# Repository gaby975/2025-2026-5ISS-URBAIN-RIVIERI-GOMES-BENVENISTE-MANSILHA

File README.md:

# 2025-2026-5ISS-URBAIN-RIVIERI-GOMES-BENVENISTE-MANSILHA
## Introduction
The objective of this project is to develop an electronic card on which we have integrated a gas sensor manufactured in the clean room at AIME (Inter-University Micro-Nano Electronics Laboratory). The electronic board includes an analog circuit for conditioning the sensor signal, a microcontroller (ESP32) for receiving the conditioned sensor signal and communicating with the other components on the board, a LoRa module for sending sensor data over a LoRa network using Chirpstack, and a buzzer to alert when a gas concentration threshold has been exceeded.

## Gas sensor fabrication
The first step in this project is to manufacture a gas sensor. This sensor was manufactured in a clean room at the AIME (Interuniversity Micro-Nano Electronics Workshop) located on the INSA Toulouse campus. It is a semiconductor-type metal oxide gas sensor based on WO₃ nanoparticles and capable of detecting reducing gases such as ammonia (NH₃) and ethanol vapors.

The sensor is composed of several elements that are worth detailing. First, there are interdigitated aluminum combs on which WO₃ nanoparticles have been deposited and organized by dielectrophoresis. Next, there is an n-doped polysilicon heating resistor, which raises the temperature inside the sensor, improving the surface reaction between the WO₃ nanoparticles and the gas. Finally, there is an aluminum thermistor that measures the temperature inside the sensor.

The manufacturing process for this sensor involves a large number of steps, but the most important ones are the photolithography steps. Photolithography enables the formation of the different layers required for the sensor to function. We start with a Si/SiO₂ substrate onto which a layer of polysilicon is deposited using the Low Pressure Chemical Vapor Deposition (LPCVD) technique. The polysilicon is n-doped by diffusing phosphorus (P) into it. An initial photolithography step is used to obtain the correct pattern for the polysilicon layer. A second photolithography step is then used to create the SiO₂ insulation layer with openings. Finally, a last photolithography step is used to create the electrodes from a deposited aluminum layer.

## Simulation on LTspice
As part of this project, one part was dedicated to designing a stage for conditioning/amplifying the signal delivered by the gas sensor. This signal, which is processed by the ESP32-WROOM microcontroller ADC, must be readable and processable by the latter. To do this, the conditioning stage was designed around the component LTC1050, which was used because It has a really low input voltage offset as well as a good common-mode tolerance and relatively low voltage drift maintain the integrity and accuracy of the 10mV voltage measured at the terminals of R1. This is the schematic we get on LTSpice:

To ensure good signal quality, several filters have been installed. A bandwidth of 1 Hz is sufficient to extract useful information from the sensor. Three filters have been used: 

- a passive filter F1 at the input to prevent HF noise from causing distortion in the input stages: R0, C1, and R1.
- an active filter F2 at the operational amplifier level : R3 and C4.
- a passive filter F3 at the output of the circuit to remove noise introduced during processing (power supply noise, clock noise) : C2 and R6.

Using an LTspice simulation, we were able to determine the frequency response (frequency gain) of each filter and also of the entire circuit. The Bode diagram of the active filter is as follows :

The Bode diagram of the passive filter at the output of the circuit is as follows :

Finally, we find the following frequency response for the complete setup (gain and phase):

## PCB design on KiCad

After all these simulation and in parallel with the software development of the ESP32 and its interaction with the LoRa module, the electronic board diagram was entered and the complete PCB routing was carried out. The electronic board diagram includes female connectors to facilitate the integration of the microcontroller and the LoRa module. With that a two-pins connector is included to ensure the correct power supply to the gas sensor's heating element. A buzzer has also been added to provide audible alerts when gas is detected, as well as a button for various uses, such as sending data or requesting a connection with the LoRa gateway. 

#### Here is the electrical schematic of the board:

#### We gathered all the components we used for this board: 

| Reference        | Quantity | Value / Description         | 
|------------------|----------|-----------------------------|
| BZ1              | 1        | Buzzer                      | 
| C1, C3, C4       | 3        | 100 nF                      | 
| C2               | 1        | 1 µF                        | 
| J1               | 1        | Connector  1x02             | 
| J2               | 1        | Connector  module LoRa      | 
| J3               | 1        | Connector  femelle ESP      | 
| R1, R6, R8       | 3        | 10 kΩ                       | 
| R2, R4           | 2        | 100 kΩ                      | 
| R3, R5           | 2        | 1 kΩ                        | 
| SW2              | 1        | Push button                 | 
| U2               | 1        | Gaz Sensor                  | 
| U3               | 1        | LTC1050CN8-PBF (AOP)        | 

The electronic board diagram done, the PCB routing has been done and the goal was to minimized the size of the whole card. As a result, we decided to route on both sides (top and bottom) to save space and make it compact and to outsource PCB manufacturing to JLC PCB to have a more clean product. 

#### Here is the final PCB layout: 

## Embedded code

This program (Arduino/ESP32) reads a **gas sensor** on an analog input, computes an estimated value in **PPM**, then sends it to **ChirpStack** via an **RN2483** module using **LoRaWAN OTAA**.
Transmission happens **every 5 seconds** or **when the button is pressed**. An **LED** indicates sending, and a **buzzer** beeps on each transmission to indicate **SUCCESS** or **FAILURE**.

---

### Required hardware

* ESP32
* RN2xx3 LoRa module (RN2483 / RN2903) connected via UART
* Gas sensor (analog output)
* Button (digital input)
* Buzzer (digital output)
* Built-in LED (or external LED)

---

### Pinout (ESP32 ↔ RN2xx3 / Sensors / I/O)

#### LoRa RN2483 (UART2 / Serial2)

| Function   | ESP32 GPIO | Direction      | RN2483         |
| ---------- | ---------: | -------------- | -------------- |
| UART2 RX   | **GPIO16** | ESP32 receives | RN2483 **TX**  |
| UART2 TX   | **GPIO17** | ESP32 sends    | RN2483 **RX**  |
| LoRa Reset |  **GPIO4** | output         | RN2483 **RST** |
| Power      |   **3.3V** | —              | VCC            |
| Ground     |    **GND** | —              | GND            |

---

#### Sensors / Button / Buzzer / LED

| Element                 | ESP32 GPIO | Type   | Note                                                   |
| ----------------------- | ---------: | ------ | ------------------------------------------------------ |
| Gas sensor (analog)     | **GPIO36** | ADC1   | reads the analog value after the filter                |
| Button                  | **GPIO22** | input  | wired in pull-up mode                                  |
| Buzzer                  | **GPIO23** | output | beep on each send                                      |
| LED (built-in)          |  **GPIO2** | output | LED on while sending                                   |
| “Temperature” (analog ) |  **GPIO2** | input  | reads the analog value aftera a voltage divider        |

---

### Dependencies

#### Arduino library

* `rn2xx3`

Include in the code:

```cpp
#include <rn2xx3.h>
```

## Node-RED

The Node-RED flow listens to an MQTT topic (ChirpStack uplinks), **extracts the `data` field**, **decodes it from Base64**, then **converts it to a base-10 number**. The value is displayed on a **dashboard** (gauge + history). A **“DANGER!”** alert (text + audio) is triggered above a threshold.

### Features

* **MQTT In**

  * Broker: `srv-chirpstack.insa-toulouse.fr:1883`
  * Topic: `application/2fc05488-1aaa-49cf-a35a-cf58fae84647/device/0004a30b0110c16d/event/up`
  * QoS: `2`
* **Decoding**

  * Extract `payload.data`
  * `Base64 -> UTF-8 -> Number (base 10)`
* **Dashboard**

  * Gauge `Actual_Sensor_Value` (0 → 8000, green/yellow/red zones)
  * Chart `Sensor_value_History` (~1h history)
* **Alert**

  * If `value >= 6000` → `DANGER!` + audio + text

### Prerequisites

* Node-RED installed
* Network access to the MQTT broker
* Node-RED modules:

  * `node-red-dashboard` (the flow indicates config **3.6.6**)
  * The `ui_audio` node may require an additional module depending on your setup (often `node-red-contrib-ui-audio`)

Example installation:

```bash
cd ~/.node-red
npm install node-red-dashboard
# if needed (if ui_audio is "unknown node type")
npm install node-red-contrib-ui-audio
```

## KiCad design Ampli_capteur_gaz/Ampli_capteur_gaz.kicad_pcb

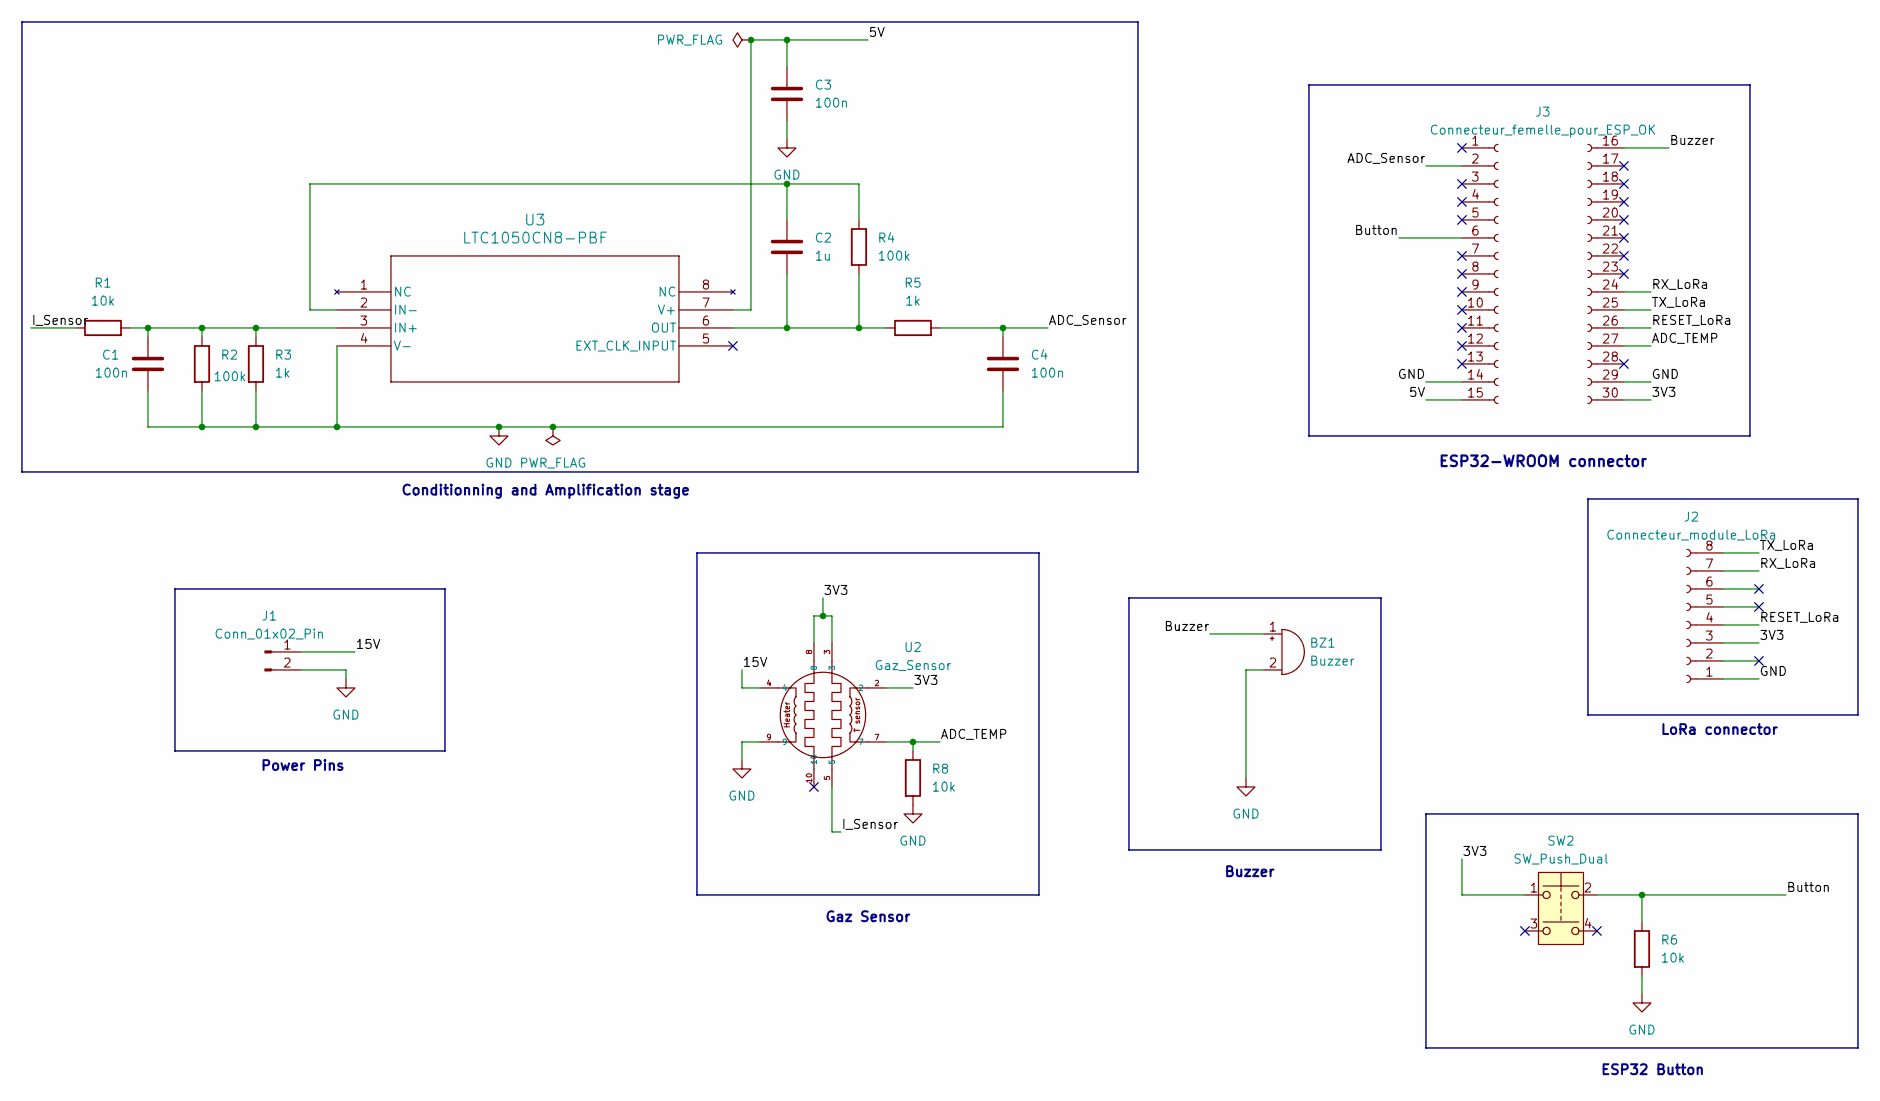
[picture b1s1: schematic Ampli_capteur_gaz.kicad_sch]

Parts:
BZ1: Buzzer; Buzzer_12x9.5RM7.6
C1, C3, C4: 100n; C_1206_3216Metric_Pad1.33x1.80mm_HandSolder
C2: 1u; C_1206_3216Metric_Pad1.33x1.80mm_HandSolder
J1: Conn_01x02_Pin; PinHeader_1x02_P2.54mm_Vertical
J2: Connecteur_module_LoRa; PinSocket_1x08_P2.54mm_Vertical
J3: Connecteur_femelle_pour_ESP_OK; Connecteur femelle ESP
R1, R6, R8: 10k; R_1206_3216Metric_Pad1.30x1.75mm_HandSolder
R2, R4: 100k; R_1206_3216Metric_Pad1.30x1.75mm_HandSolder
R3, R5: 1k; R_1206_3216Metric_Pad1.30x1.75mm_HandSolder
SW2: SW_Push_Dual; SW_PUSH-12mm
U2: Gaz_Sensor; TO-5-10
U3: LTC1050CN8-PBF; PDIP-8_N_LIT

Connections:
/3V3: J2.3, J3.30 (Pin_1), SW2.1, U2.2, U2.3, U2.8
/5V: C3.1, J3.15, U3.7 (V+)
/15V: J1.1, U2.4
/ADC_Sensor: C4.1, J3.2, R5.2
/ADC_TEMP: J3.27, R8.1, U2.7
/Button: J3.6, R6.1, SW2.2
/Buzzer: BZ1.1 (+), J3.16 (Pin_15)
/I_Sensor: R1.1, U2.5
/RESET_LoRa: J2.4, J3.26 (Pin_5)
/RX_LoRa: J2.7, J3.24
/TX_LoRa: J2.8, J3.25 (Pin_6)
GND: BZ1.2 (-), C1.2, C3.2, C4.2, J1.2, J2.1, J3.14, J3.29 (Pin_2), R2.2, R3.2, R6.2, R8.2, U2.9, U3.4 (V-)
unnamed: C1.1, R1.2, R2.1, R3.1, U3.3 (IN+)
unnamed: C2.1, R4.1, U3.2 (IN-)
unnamed: C2.2, R4.2, R5.1, U3.6 (OUT)

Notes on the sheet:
ESP32 Button
LoRa connector
Power Pins
Buzzer
Conditionning and Amplification stage
ESP32-WROOM connector
Gaz Sensor

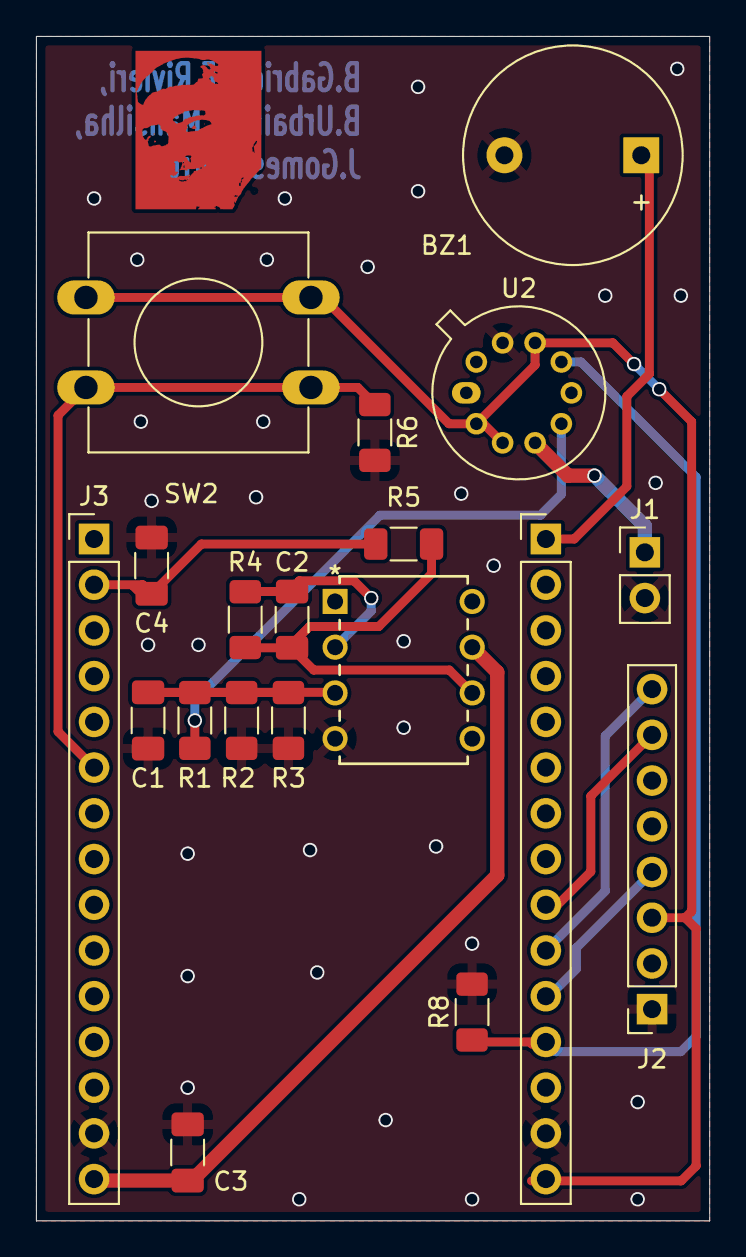
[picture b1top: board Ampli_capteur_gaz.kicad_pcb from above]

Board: 2 copper layers, 37.4 x 65.8 mm, 18 parts (0 on the bottom side), 15 nets.

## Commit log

2026-01-06 Ajout_node_red
2026-01-06 modif readme
2026-01-06 Fin Node red
2026-01-06 ajout image
2026-01-06 titres
2026-01-06 readme
2026-01-09 Ajout readme
2026-01-09 KiCad files added
2026-01-09 ajout
2026-01-09 Readme traduit
2026-01-09 Kicad update
2026-01-09 retrait conclu
